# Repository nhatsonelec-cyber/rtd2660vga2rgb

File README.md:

# RTD2660 VGA (header 12P) → LVDS 20P cho màn 7" 1024x600

Mạch điều khiển màn hình dùng chip Realtek **RTD2660**, thiết kế theo datasheet trong repo (`RTD2660.jsp.pdf`).

- **Đầu vào:** VGA trên **header 12 chân 2.54 mm**, cắm thẳng vào header VGA trên mainboard.
- **Đầu ra:** LVDS 1 kênh, 24 bit trên **đầu 20 chân 2.0 mm (J5)**, cùng **đầu đèn nền 4 chân 2.0 mm (J6)**.
  Hai đầu này khớp với cáp của màn 7" IPS 1024x600 LVDS 20 chân (Huadi).
- **Bản RGB 40P/50P tạm bỏ.** Mạch của chúng vẫn còn trong `tools/circuit.py` để làm sau.

| File | Nội dung |
|---|---|
| `eagle/RTD2660_VGA12P_LVDS.sch` | Sơ đồ nguyên lý, 4 trang |
| `eagle/RTD2660_VGA12P_LVDS.brd` | Board 120 x 80 mm, linh kiện đã đặt ở mặt trên, chưa đi dây |
| `eagle/rtd2660_board.lbr` | Thư viện linh kiện |
| `eagle/RTD2660_VGA12P_LVDS_BOM.csv` | Danh sách linh kiện |
| `preview/RTD2660_VGA12P_LVDS_preview.pdf` | Bản xem trước sơ đồ và board |
| `firmware/` | Script cấu hình firmware cho SDK RTD2660 |

## Trạng thái

- **Sơ đồ nguyên lý: xong.** Các net nối bằng nhãn tên.
- **Board: toàn bộ 114 linh kiện đặt ở mặt trên, chưa đi dây.** Có sẵn polygon GND ở mặt dưới.
- Mở bằng Eagle 7.x, 8.x hoặc 9.x. File `.brd` mở kèm và nhất quán với sơ đồ.
- **Đã kiểm tra:** KiCad đọc được file `.brd`, netlist khớp 100% từng pad với sơ đồ. DRC không có linh kiện chồng nhau.
  `tools/check_eagle.py` xác nhận mọi chân nằm trên lưới 0.1 inch.
- Khi đi dây, đi các cặp LVDS thành cặp vi sai 100 Ω, ngắn và bằng chiều dài. Thêm via tản nhiệt dưới pad GND của RTD2660.

## Sơ đồ chân các đầu nối

**J2 - VGA 1x12, 2.54 mm (đầu vào)**

| Chân | Tín hiệu |
|---|---|
| 1 | VGA_R |
| 2 | GND |
| 3 | VGA_G |
| 4 | GND |
| 5 | VGA_B |
| 6 | GND |
| 7 | VGA_HS |
| 8 | VGA_VS |
| 9 | GND |
| 10 | VGA_SDA |
| 11 | VGA_SCL |
| 12 | VGA_5V |

Chân 12 (+5V từ mainboard) không dùng. Nếu header VGA trên mainboard có thứ tự khác, sửa `VGA12_PINOUT` trong `tools/circuit.py`.

**J5 - LVDS 1x20, 2.0 mm (đầu đen của cáp màn)**

| Chân | Tín hiệu |
|---|---|
| 1 | VLCD |
| 2 | VLCD |
| 3 | PNL_LED_EN |
| 4 | GND |
| 5 | LVDS_E0- |
| 6 | LVDS_E0+ |
| 7 | GND |
| 8 | LVDS_E1- |
| 9 | LVDS_E1+ |
| 10 | GND |
| 11 | LVDS_E2- |
| 12 | LVDS_E2+ |
| 13 | GND |
| 14 | LVDS_EC- |
| 15 | LVDS_EC+ |
| 16 | GND |
| 17 | LVDS_E3- |
| 18 | LVDS_E3+ |
| 19 | không dùng |
| 20 | không dùng |

Chân 1-18 giống hệt sơ đồ chân của màn. Ở chế độ 1 kênh, RTD2660 xuất trên các cặp E (chân 86-95 của chip).

**J6 - đèn nền 1x4, 2.0 mm (đầu trắng của cáp màn)**

| Chân | Tín hiệu |
|---|---|
| 1 | +12V |
| 2 | PNL_LED_EN |
| 3 | PNL_BL_ADJ |
| 4 | GND |

**Thứ tự chân J6 là giả định.** Hãy đo cáp bằng đồng hồ: VLED nối chân 20 của màn, PWM nối chân 19, LED_EN nối chân 3.
Nếu khác, sửa `BL4_PINOUT` trong `tools/circuit.py` rồi chạy lại script.

- Chân độ sáng ra điện áp DC từ 0 đến 1.41 V, lấy từ PWM4 qua bộ lọc 10k / 7.5k / 1 µF. Màn nhận 0.7 đến 1.4 V.
- LED_EN lấy từ BL_ON qua 1k, có 10k kéo xuống.
- VLED lấy thẳng từ +12 V. Màn nhận 5 đến 12 V.

Các đầu nối khác:

- **J1, nguồn vào 12 V:** 1 = +12V, 2 = GND. Có cầu chì PTC 2 A và diode chống ngược.
- **J3, nạp firmware qua DDC:** GND, SDA, SCL.
- **J4, phím và IR (1x8):** 1 +3V3, 2 GND, 3 KEY_AD0, 4 KEY_AD1, 5 IR, 6 LED_G, 7 LED_R, 8 +5V.

## Nguồn

12 V → LM2596S-5.0 → 5 V. Từ 5 V có hai AMS1117-3.3: một cho phần số (PVCC, flash) và một cho phần analog (VDD, VADC).
Từ đó hai AMS1117-1.8 tạo VCCK (lõi) và ADC_VDD.
VDD 3.3 V của màn lấy từ một AMS1117-3.3 riêng, được bật bằng MOSFET AO3401A theo chân PANEL_ON.

## Bàn phím (J4)

SDK đọc phím bằng một kênh ADC 6 bit (KEY_AD0, chân 50). Trên board đã có điện trở kéo lên 10k.
Trên bo phím, mỗi nút nối KEY_AD0 xuống GND qua một điện trở:

| Nút | Điện trở xuống GND | Mã ADC |
|---|---|---|
| POWER | 0 Ω | 0 |
| MENU | 1.8k | 10 |
| RIGHT | 3.9k | 18 |
| LEFT | 8.2k | 28 |
| SOURCE | 22k | 43 |

## Gán chân GPIO

| Chân | Chức năng chip | Net | Dùng cho |
|---|---|---|---|
| 50 | P6.0 / A-ADC0 | KEY_AD0 | Keypad resistor ladder 1 (ADC) |
| 51 | P6.1 / A-ADC1 | KEY_AD1 | Keypad resistor ladder 2 (ADC) |
| 52 | P6.2 | LED_R_DRV | Red / standby LED, active high |
| 53 | P6.3 | LED_G_DRV | Green / power LED, active high |
| 58 | DDCSCL1 (P3.0) | DDC_SCL | VGA DDC clock, ISP programming |
| 59 | DDCSDA1 (P3.1) | DDC_SDA | VGA DDC data, ISP programming |
| 98 | P5.4 | PANEL_ON | Panel power enable, active high |
| 99 | P5.5 | BL_ON | Backlight enable, active high |
| 100 | P5.6 / PWM4 | BL_PWM | Backlight brightness PWM, high = bright |
| 113 | P3.6 / IrDA | IR_IN | IR receiver input |

## Firmware

RTD2660 cần firmware trong flash W25Q40. Xem `firmware/README.md`.
Script áp cấu hình board và màn 1024x600 lên SDK RTD2660, sau đó biên dịch bằng Keil C51.

## Những điểm cần kiểm tra

1. **Thạch anh 27 MHz**, giống board tham chiếu PCB800099 của SDK.
2. **Chân SPI flash.** Tên chân (115 SCLK, 116 SI, 117 SO) và phần mô tả trong datasheet lệch nhau ở chân 115/116.
   Mạch theo tên chân. Có sẵn cặp điện trở 33R (không hàn) để đảo CLK/DI nếu flash không chạy.
3. **Thứ tự chân header VGA 12P và đầu đèn nền 4 chân.** Phải khớp với mainboard và cáp màn.
4. **Timing màn** (tổng 1344 x 635, 51.2 MHz) là giá trị phổ biến của màn 7" 1024x600. Nếu có datasheet màn, đối chiếu lại.

## Sửa thiết kế

```bash
pip install lxml matplotlib
python3 tools/gen_eagle.py      # sinh file Eagle và BOM
python3 tools/check_eagle.py    # kiểm tra
python3 tools/preview.py        # sinh bản xem trước PDF
```

- `tools/circuit.py`: mạch điện, sơ đồ chân các đầu nối, bảng GPIO
- `tools/parts.py`: ký hiệu, footprint, sơ đồ chân RTD2660
- `tools/gen_eagle.py`: ghi file Eagle và đặt linh kiện trên board
- `firmware/apply_board.py`: áp cấu hình board và màn lên SDK firmware RTD2660

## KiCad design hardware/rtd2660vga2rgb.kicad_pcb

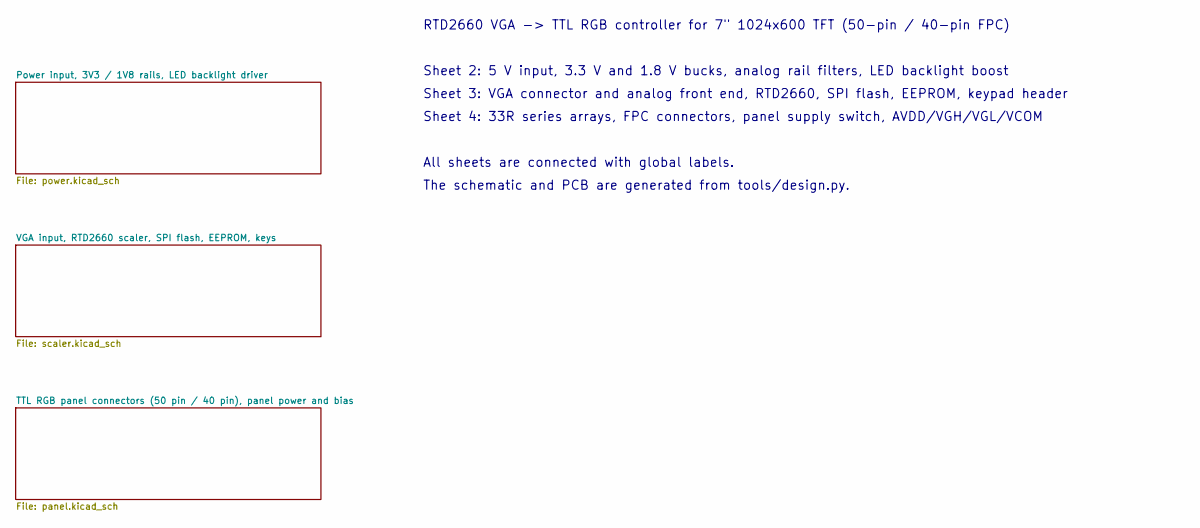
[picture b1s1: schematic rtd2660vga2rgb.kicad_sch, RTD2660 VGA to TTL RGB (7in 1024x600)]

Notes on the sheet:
RTD2660 VGA -> TTL RGB controller for 7" 1024x600 TFT (50-pin / 40-pin FPC)
Sheet 2: 5 V input, 3.3 V and 1.8 V bucks, analog rail filters, LED backlight boost
Sheet 3: VGA connector and analog front end, RTD2660, SPI flash, EEPROM, keypad header
Sheet 4: 33R series arrays, FPC connectors, panel supply switch, AVDD/VGH/VGL/VCOM
All sheets are connected with global labels.
The schematic and PCB are generated from tools/design.py.

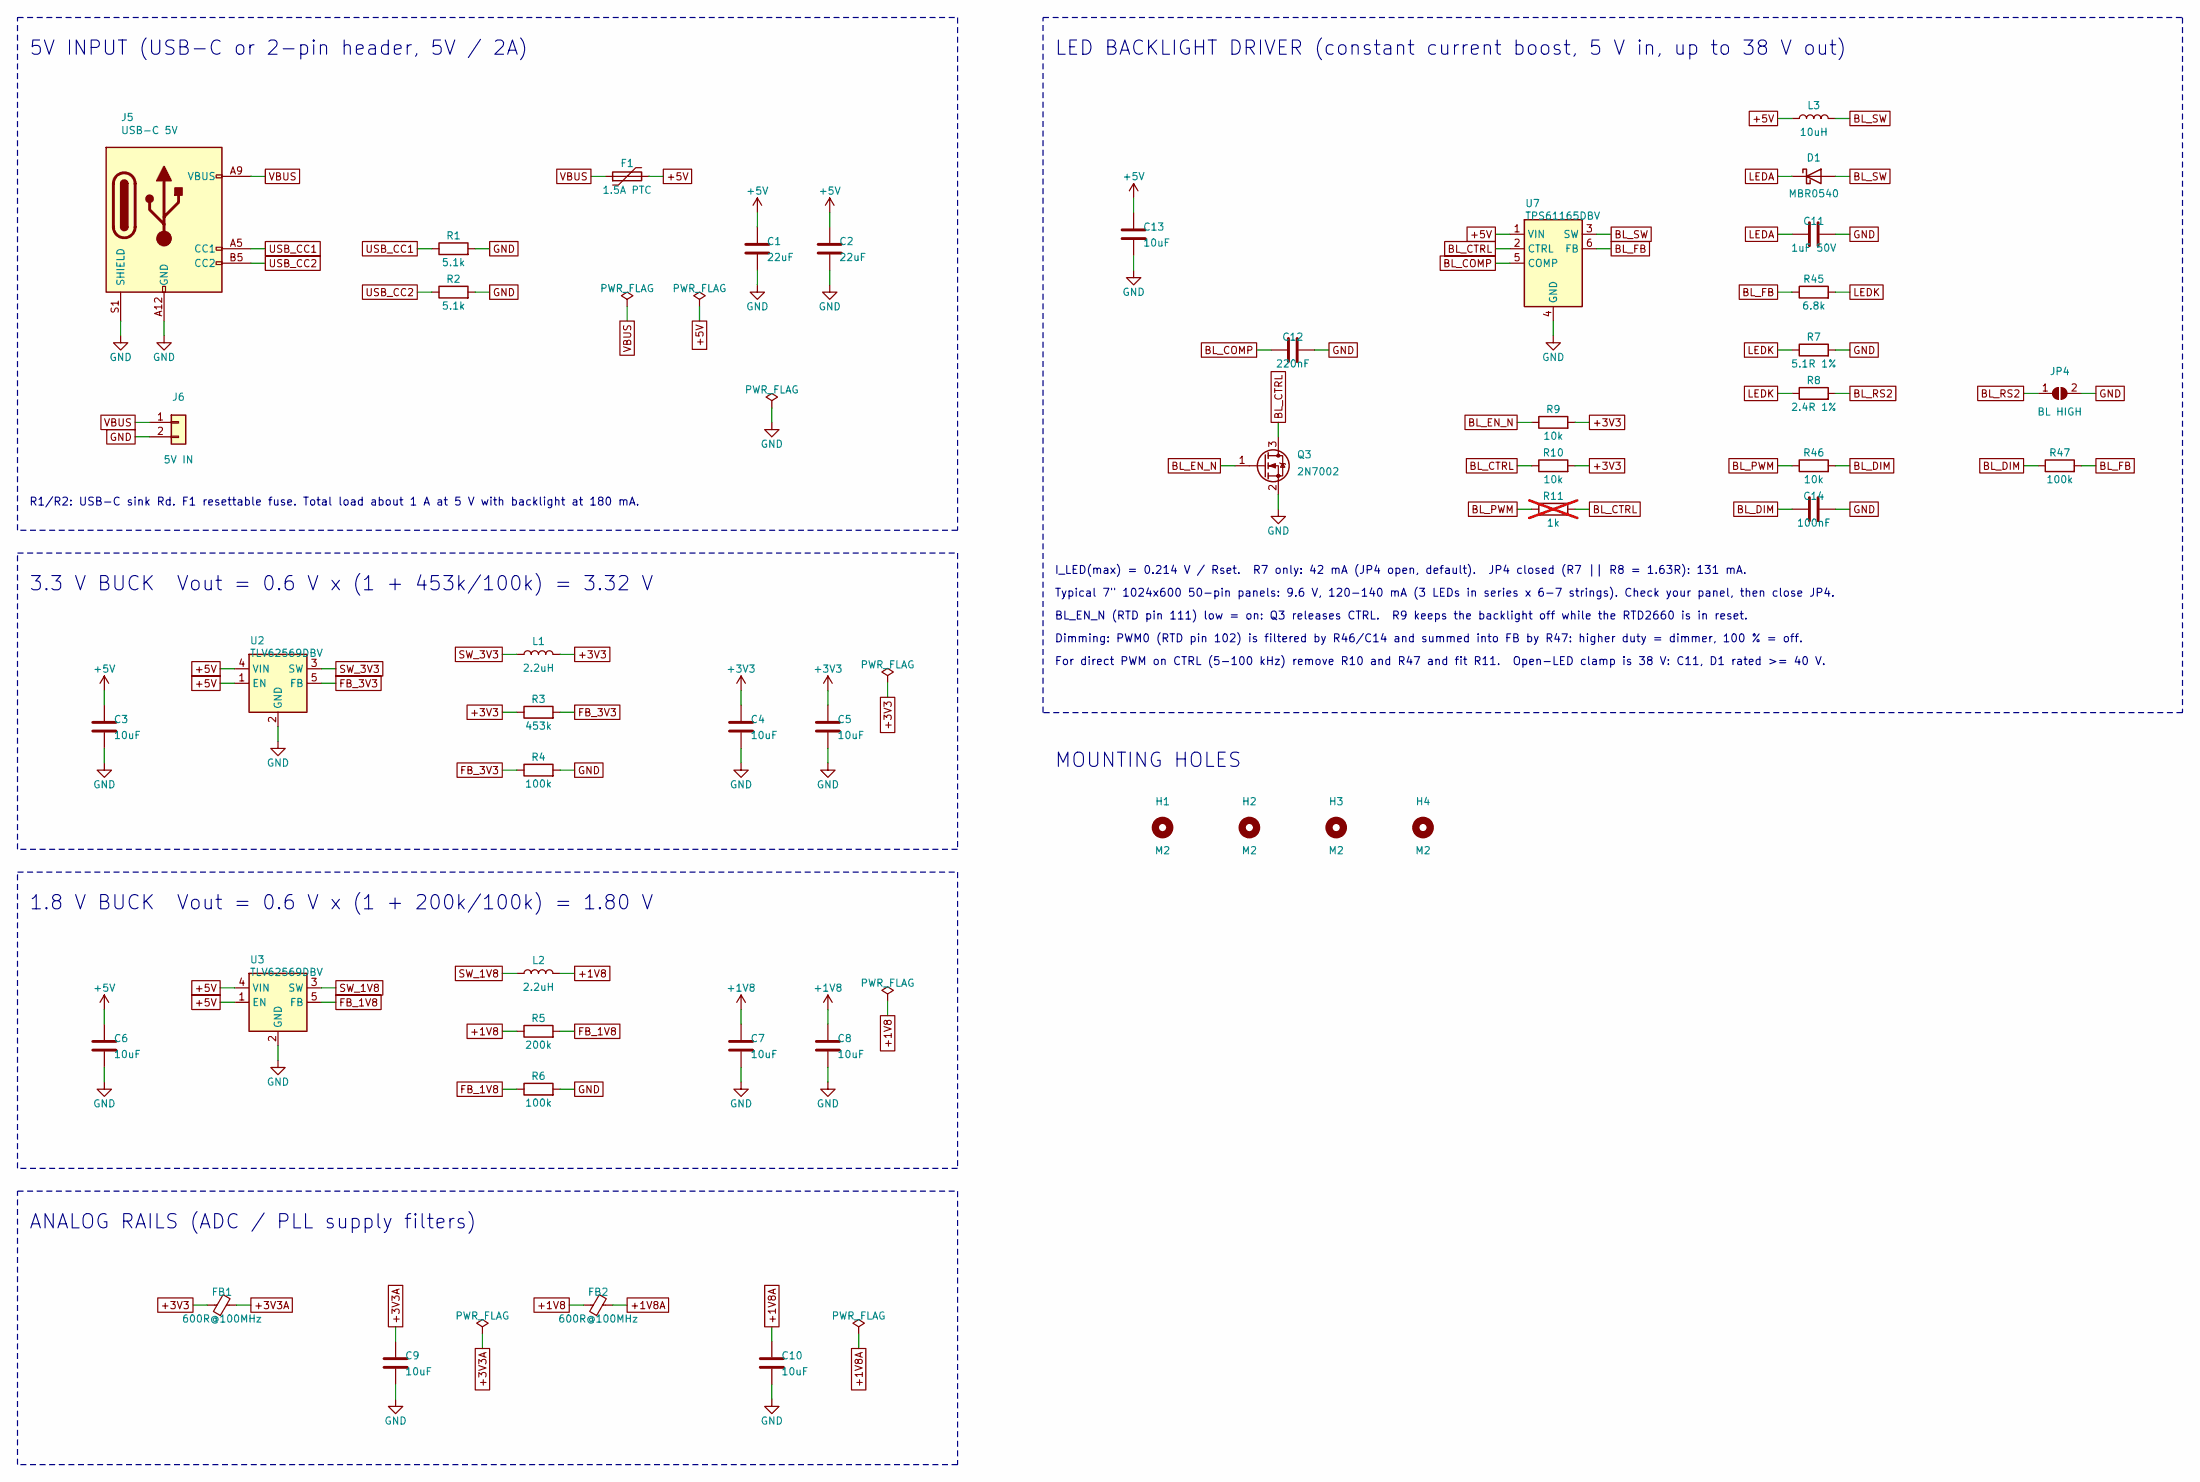
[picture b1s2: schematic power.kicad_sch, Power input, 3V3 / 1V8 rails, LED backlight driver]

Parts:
C1, C2: 22uF; C_0805_2012Metric
C3, C4, C5, C6, C7, C8, C9, C10, C13: 10uF; C_0805_2012Metric
C11: 1uF 50V; C_0805_2012Metric
C12: 220nF; C_0603_1608Metric
C14: 100nF; C_0603_1608Metric
D1: MBR0540; D_SOD-123
F1: 1.5A PTC; Fuse_1206_3216Metric
FB1, FB2: 600R@100MHz; L_0603_1608Metric
H1, H2, H3, H4: M2; MountingHole_2.2mm_M2
J5: USB-C 5V; USB_C_Receptacle_GCT_USB4125-xx-x_6P_TopMnt_Horizontal
J6: 5V IN; PinHeader_1x02_P2.54mm_Vertical
JP4: BL HIGH; SolderJumper-2_P1.3mm_Open_RoundedPad1.0x1.5mm
L1, L2: 2.2uH; L_Taiyo-Yuden_NR-30xx
L3: 10uH; L_Taiyo-Yuden_NR-40xx
Q3: 2N7002; SOT-23
R1, R2: 5.1k; R_0603_1608Metric
R3: 453k; R_0603_1608Metric
R4, R6, R47: 100k; R_0603_1608Metric
R5: 200k; R_0603_1608Metric
R7: 5.1R 1%; R_0603_1608Metric
R8: 2.4R 1%; R_0603_1608Metric
R9, R10, R46: 10k; R_0603_1608Metric
R11: 1k; R_0603_1608Metric; not fitted
R45: 6.8k; R_0603_1608Metric
U2, U3: TLV62569DBV; SOT-23-5
U7: TPS61165DBV; SOT-23-6

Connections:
+1V8: C7.1, C8.1, FB2.1, L2.2, R5.1; also elsewhere on the board
+1V8A: C10.1, FB2.2; also elsewhere on the board
+3V3: C4.1, C5.1, FB1.1, L1.2, R3.1, R9.2, R10.2; also elsewhere on the board
+3V3A: C9.1, FB1.2; also elsewhere on the board
+5V: C1.1, C2.1, C3.1, C6.1, C13.1, F1.2, L3.1, U2.1 (EN), U2.4 (VIN), U3.1 (EN), U3.4 (VIN), U7.1 (VIN); also elsewhere on the board
BL_COMP: C12.1, U7.5 (COMP)
BL_CTRL: Q3.3 (D), R10.1, R11.2, U7.2 (CTRL)
BL_DIM: C14.1, R46.2, R47.1
BL_EN_N: Q3.1 (G), R9.1; also elsewhere on the board
BL_FB: R45.1, R47.2, U7.6 (FB)
BL_PWM: R11.1, R46.1; also elsewhere on the board
BL_RS2: JP4.1 (A), R8.2
BL_SW: D1.2 (A), L3.2, U7.3 (SW)
FB_1V8: R5.2, R6.1, U3.5 (FB)
FB_3V3: R3.2, R4.1, U2.5 (FB)
GND: C1.2, C2.2, C3.2, C4.2, C5.2, C6.2, C7.2, C8.2, C9.2, C10.2, C11.2, C12.2, C13.2, C14.2, J5.A12 (GND), J5.B12 (GND), J5.S1 (SHIELD), J6.2, JP4.2 (B), Q3.2 (S), R1.2, R2.2, R4.2, R6.2, R7.2, U2.2 (GND), U3.2 (GND), U7.4 (GND); also elsewhere on the board
LEDA: C11.1, D1.1 (K); also elsewhere on the board
LEDK: R7.1, R8.1, R45.2; also elsewhere on the board
SW_1V8: L2.1, U3.3 (SW)
SW_3V3: L1.1, U2.3 (SW)
USB_CC1: J5.A5 (CC1), R1.1
USB_CC2: J5.B5 (CC2), R2.1
VBUS: F1.1, J5.A9 (VBUS), J5.B9 (VBUS), J6.1

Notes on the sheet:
5V INPUT (USB-C or 2-pin header, 5V / 2A)
R1/R2: USB-C sink Rd. F1 resettable fuse. Total load about 1 A at 5 V with backlight at 180 mA.
3.3 V BUCK Vout = 0.6 V x (1 + 453k/100k) = 3.32 V
1.8 V BUCK Vout = 0.6 V x (1 + 200k/100k) = 1.80 V
ANALOG RAILS (ADC / PLL supply filters)
LED BACKLIGHT DRIVER (constant current boost, 5 V in, up to 38 V out)
I_LED(max) = 0.214 V / Rset. R7 only: 42 mA (JP4 open, default). JP4 closed (R7 || R8 = 1.63R): 131 mA.
Typical 7" 1024x600 50-pin panels: 9.6 V, 120-140 mA (3 LEDs in series x 6-7 strings). Check your panel, then close JP4.
BL_EN_N (RTD pin 111) low = on: Q3 releases CTRL. R9 keeps the backlight off while the RTD2660 is in reset.
Dimming: PWM0 (RTD pin 102) is filtered by R46/C14 and summed into FB by R47: higher duty = dimmer, 100 % = off.
For direct PWM on CTRL (5-100 kHz) remove R10 and R47 and fit R11. Open-LED clamp is 38 V: C11, D1 rated >= 40 V.
MOUNTING HOLES

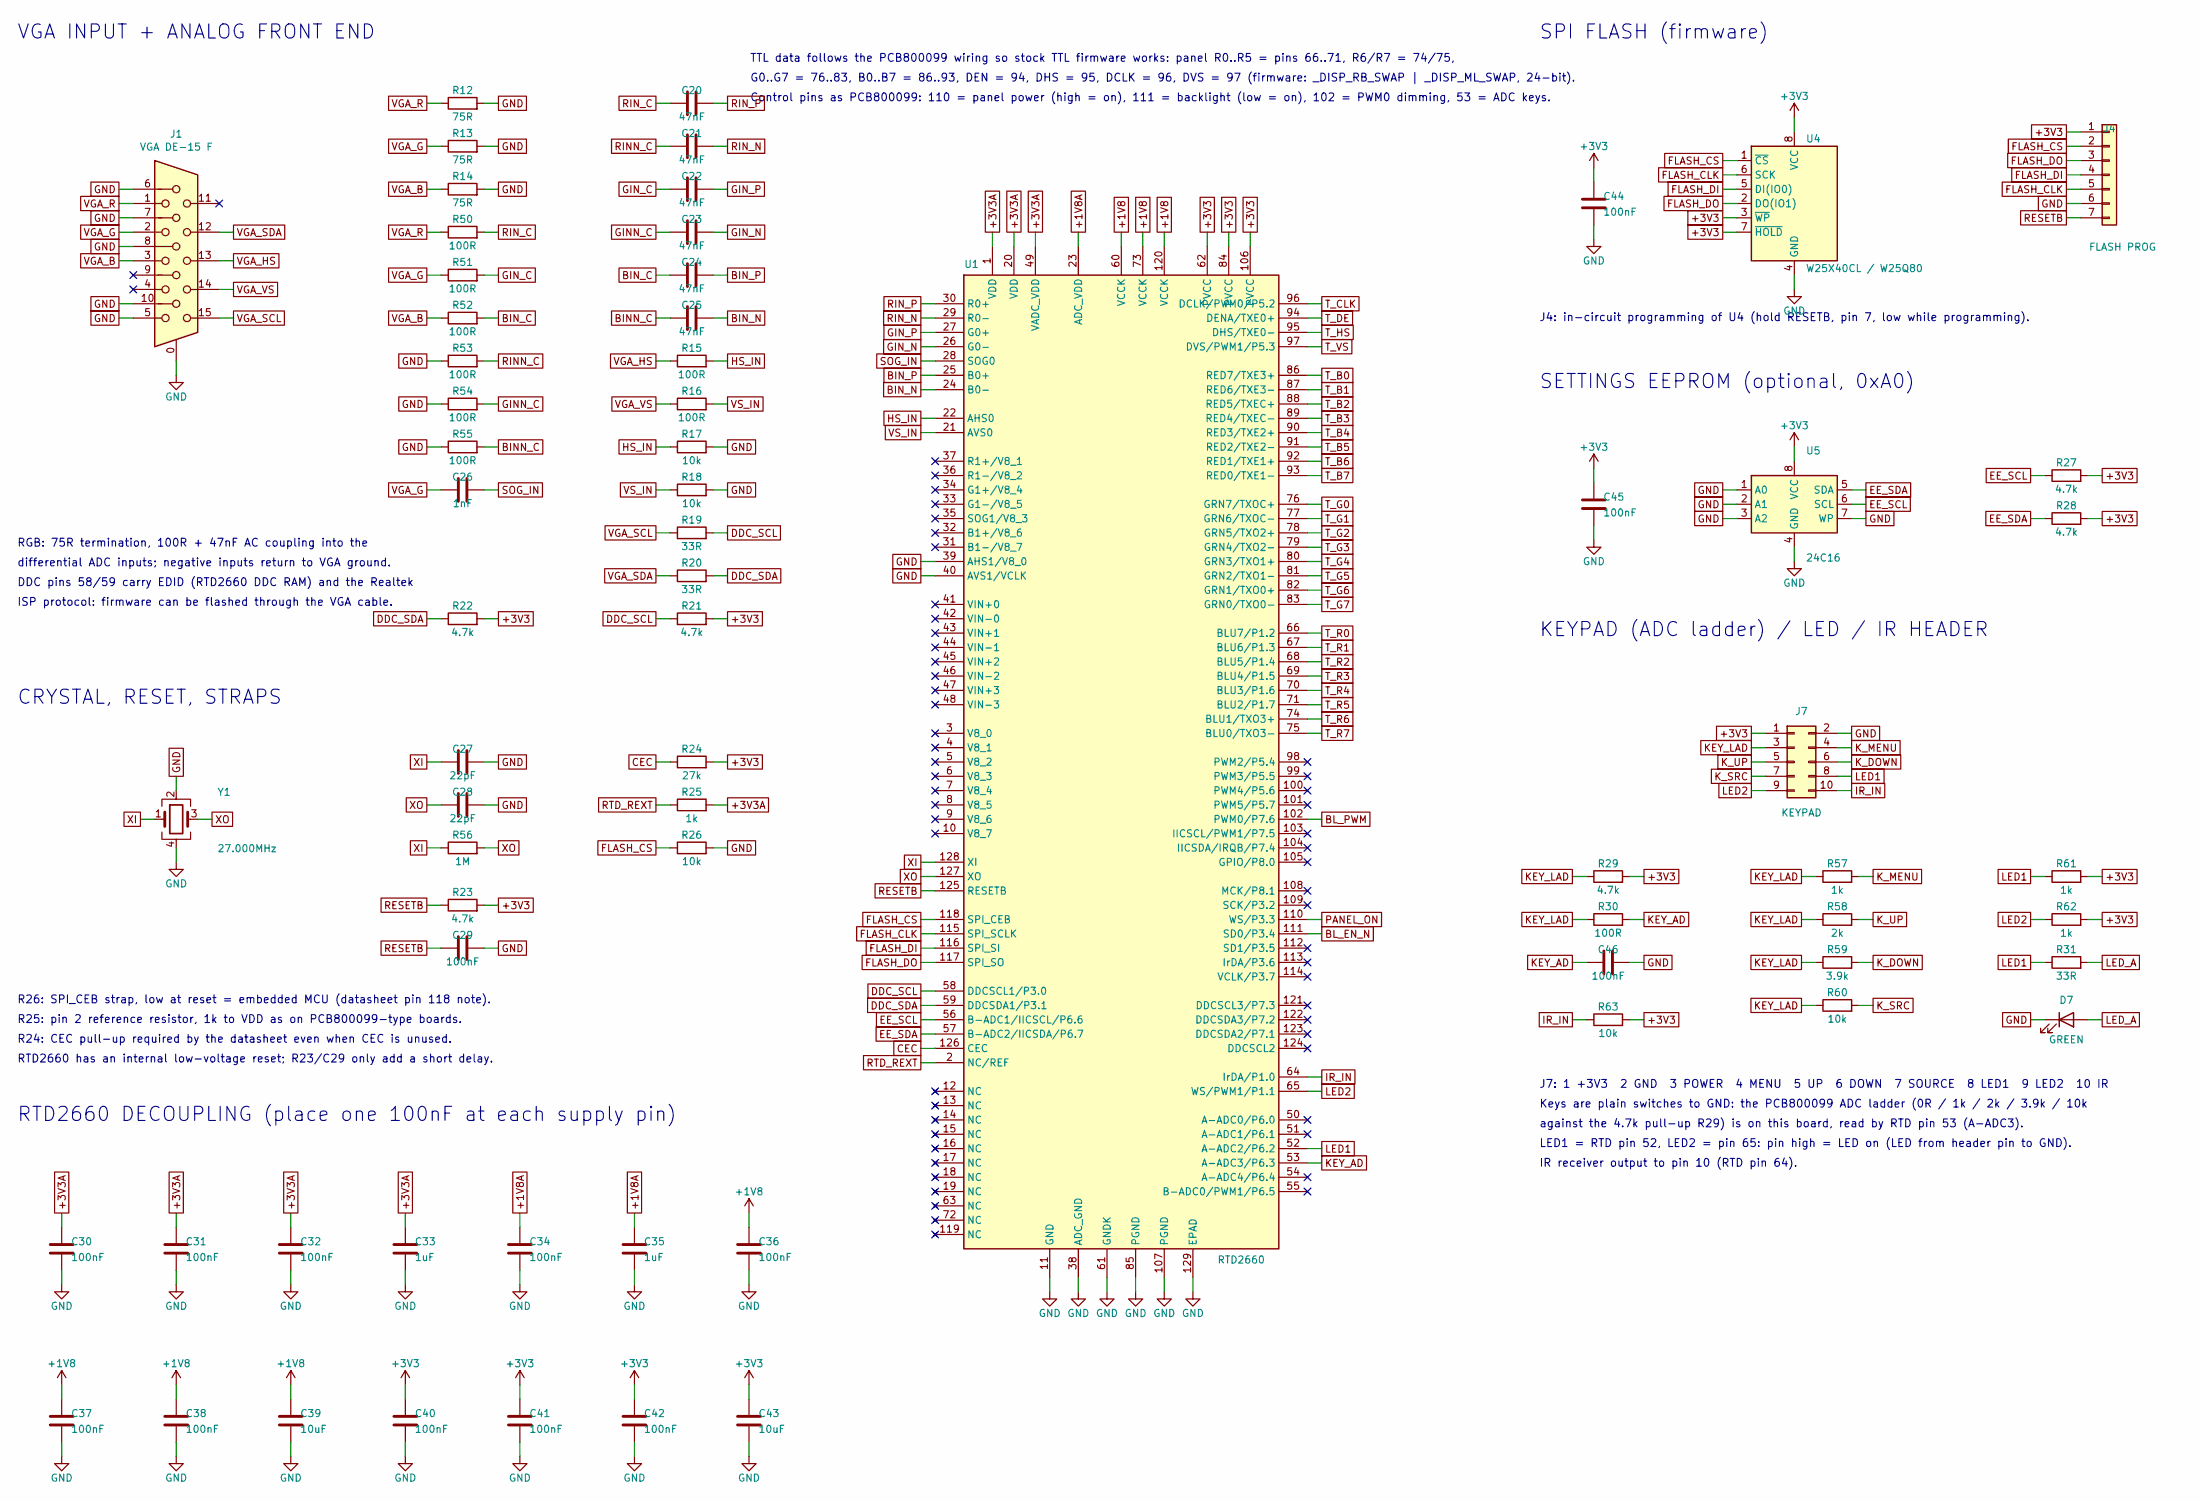
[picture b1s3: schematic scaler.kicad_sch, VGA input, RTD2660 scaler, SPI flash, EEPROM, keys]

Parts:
C20, C21, C22, C23, C24, C25: 47nF; C_0603_1608Metric
C26: 1nF; C_0603_1608Metric
C27, C28: 22pF; C_0603_1608Metric
C29, C30, C31, C32, C34, C36, C37, C38, C40, C41, C42, C44, C45, C46: 100nF; C_0603_1608Metric
C33, C35: 1uF; C_0603_1608Metric
C39, C43: 10uF; C_0805_2012Metric
D7: GREEN; LED_0603_1608Metric
J1: VGA DE-15 F; DSUB-15-HD_Female_Horizontal_P2.29x1.98mm_EdgePinOffset3.03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
J4: FLASH PROG; PinHeader_1x07_P1.27mm_Vertical
J7: KEYPAD; PinHeader_2x05_P1.27mm_Vertical_SMD
R12, R13, R14: 75R; R_0603_1608Metric
R15, R16, R30, R50, R51, R52, R53, R54, R55: 100R; R_0603_1608Metric
R17, R18, R26, R60, R63: 10k; R_0603_1608Metric
R19, R20, R31: 33R; R_0603_1608Metric
R21, R22, R23, R27, R28, R29: 4.7k; R_0603_1608Metric
R24: 27k; R_0603_1608Metric
R25, R57, R61, R62: 1k; R_0603_1608Metric
R56: 1M; R_0603_1608Metric
R58: 2k; R_0603_1608Metric
R59: 3.9k; R_0603_1608Metric
U1: RTD2660; LQFP-128-1EP_14x20mm_P0.5mm_EP7.1x7.1mm
U4: W25X40CL / W25Q80; SOIC-8_3.9x4.9mm_P1.27mm
U5: 24C16; SOIC-8_3.9x4.9mm_P1.27mm
Y1: 27.000MHz; Crystal_SMD_3225-4Pin_3.2x2.5mm

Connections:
+1V8: C36.1, C37.1, C38.1, C39.1, U1.60 (VCCK), U1.73 (VCCK), U1.120 (VCCK); also elsewhere on the board
+1V8A: C34.1, C35.1, U1.23 (ADC_VDD); also elsewhere on the board
+3V3: C40.1, C41.1, C42.1, C43.1, C44.1, C45.1, J4.1, J7.1, R21.2, R22.2, R23.2, R24.2, R27.2, R28.2, R29.2, R61.2, R62.2, R63.2, U1.62 (PVCC), U1.84 (PVCC), U1.106 (PVCC), U4.3 (~WP), U4.7 (~HOLD), U4.8 (VCC), U5.8 (VCC); also elsewhere on the board
+3V3A: C30.1, C31.1, C32.1, C33.1, R25.2, U1.1 (VDD), U1.20 (VDD), U1.49 (VADC_VDD); also elsewhere on the board
BINN_C: C25.1, R55.2
BIN_C: C24.1, R52.2
BIN_N: C25.2, U1.24 (B0-)
BIN_P: C24.2, U1.25 (B0+)
BL_EN_N: U1.111 (SD0/P3.4); also elsewhere on the board
BL_PWM: U1.102 (PWM0/P7.6); also elsewhere on the board
CEC: R24.1, U1.126 (CEC)
DDC_SCL: R19.2, R21.1, U1.58 (DDCSCL1/P3.0)
DDC_SDA: R20.2, R22.1, U1.59 (DDCSDA1/P3.1)
EE_SCL: R27.1, U1.56 (B-ADC1/IICSCL/P6.6), U5.6 (SCL)
EE_SDA: R28.1, U1.57 (B-ADC2/IICSDA/P6.7), U5.5 (SDA)
FLASH_CLK: J4.5, U1.115 (SPI_SCLK), U4.6 (SCK)
FLASH_CS: J4.2, R26.1, U1.118 (SPI_CEB), U4.1 (~CS)
FLASH_DI: J4.4, U1.116 (SPI_SI), U4.5 (DI(IO0))
FLASH_DO: J4.3, U1.117 (SPI_SO), U4.2 (DO(IO1))
GINN_C: C23.1, R54.2
GIN_C: C22.1, R51.2
GIN_N: C23.2, U1.26 (G0-)
GIN_P: C22.2, U1.27 (G0+)
GND: C27.2, C28.2, C29.2, C30.2, C31.2, C32.2, C33.2, C34.2, C35.2, C36.2, C37.2, C38.2, C39.2, C40.2, C41.2, C42.2, C43.2, C44.2, C45.2, C46.2, D7.1 (K), J1.0, J1.5, J1.6, J1.7, J1.8, J1.10, J4.6, J7.2, R12.2, R13.2, R14.2, R17.2, R18.2, R26.2, R53.1, R54.1, R55.1, U1.11 (GND), U1.38 (ADC_GND), U1.39 (AHS1/V8_0), U1.40 (AVS1/VCLK), U1.61 (GNDK), U1.85 (PGND), U1.107 (PGND), U1.129 (EPAD), U4.4 (GND), U5.1 (A0), U5.2 (A1), U5.3 (A2), U5.4 (GND), U5.7 (WP), Y1.2, Y1.4; also elsewhere on the board
HS_IN: R15.2, R17.1, U1.22 (AHS0)
IR_IN: J7.10, R63.1, U1.64 (IrDA/P1.0)
KEY_AD: C46.1, R30.2, U1.53 (A-ADC3/P6.3)
KEY_LAD: J7.3, R29.1, R30.1, R57.1, R58.1, R59.1, R60.1
K_DOWN: J7.6, R59.2
K_MENU: J7.4, R57.2
K_SRC: J7.7, R60.2
K_UP: J7.5, R58.2
LED1: J7.8, R31.1, R61.1, U1.52 (A-ADC2/P6.2)
LED2: J7.9, R62.1, U1.65 (WS/PWM1/P1.1)
LED_A: D7.2 (A), R31.2
PANEL_ON: U1.110 (WS/P3.3); also elsewhere on the board
RESETB: C29.1, J4.7, R23.1, U1.125 (RESETB)
RINN_C: C21.1, R53.2
RIN_C: C20.1, R50.2
RIN_N: C21.2, U1.29 (R0-)
RIN_P: C20.2, U1.30 (R0+)
RTD_REXT: R25.1, U1.2 (NC/REF)
SOG_IN: C26.2, U1.28 (SOG0)
T_B0: U1.86 (RED7/TXE3+); also elsewhere on the board
T_B1: U1.87 (RED6/TXE3-); also elsewhere on the board
T_B2: U1.88 (RED5/TXEC+); also elsewhere on the board
T_B3: U1.89 (RED4/TXEC-); also elsewhere on the board
T_B4: U1.90 (RED3/TXE2+); also elsewhere on the board
T_B5: U1.91 (RED2/TXE2-); also elsewhere on the board
T_B6: U1.92 (RED1/TXE1+); also elsewhere on the board
T_B7: U1.93 (RED0/TXE1-); also elsewhere on the board
T_CLK: U1.96 (DCLK/PWM0/P5.2); also elsewhere on the board
T_DE: U1.94 (DENA/TXE0+); also elsewhere on the board
T_G0: U1.76 (GRN7/TXOC+); also elsewhere on the board
T_G1: U1.77 (GRN6/TXOC-); also elsewhere on the board
T_G2: U1.78 (GRN5/TXO2+); also elsewhere on the board
T_G3: U1.79 (GRN4/TXO2-); also elsewhere on the board
T_G4: U1.80 (GRN3/TXO1+); also elsewhere on the board
T_G5: U1.81 (GRN2/TXO1-); also elsewhere on the board
T_G6: U1.82 (GRN1/TXO0+); also elsewhere on the board
T_G7: U1.83 (GRN0/TXO0-); also elsewhere on the board
T_HS: U1.95 (DHS/TXE0-); also elsewhere on the board
T_R0: U1.66 (BLU7/P1.2); also elsewhere on the board
T_R1: U1.67 (BLU6/P1.3); also elsewhere on the board
T_R2: U1.68 (BLU5/P1.4); also elsewhere on the board
T_R3: U1.69 (BLU4/P1.5); also elsewhere on the board
T_R4: U1.70 (BLU3/P1.6); also elsewhere on the board
T_R5: U1.71 (BLU2/P1.7); also elsewhere on the board
T_R6: U1.74 (BLU1/TXO3+); also elsewhere on the board
T_R7: U1.75 (BLU0/TXO3-); also elsewhere on the board
T_VS: U1.97 (DVS/PWM1/P5.3); also elsewhere on the board
VGA_B: J1.3, R14.1, R52.1
VGA_G: C26.1, J1.2, R13.1, R51.1
VGA_HS: J1.13, R15.1
VGA_R: J1.1, R12.1, R50.1
VGA_SCL: J1.15, R19.1
VGA_SDA: J1.12, R20.1
VGA_VS: J1.14, R16.1
VS_IN: R16.2, R18.1, U1.21 (AVS0)
XI: C27.1, R56.1, U1.128 (XI), Y1.1
XO: C28.1, R56.2, U1.127 (XO), Y1.3

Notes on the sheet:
VGA INPUT + ANALOG FRONT END
RGB: 75R termination, 100R + 47nF AC coupling into the
differential ADC inputs; negative inputs return to VGA ground.
DDC pins 58/59 carry EDID (RTD2660 DDC RAM) and the Realtek
ISP protocol: firmware can be flashed through the VGA cable.
CRYSTAL, RESET, STRAPS
R26: SPI_CEB strap, low at reset = embedded MCU (datasheet pin 118 note).
R25: pin 2 reference resistor, 1k to VDD as on PCB800099-type boards.
R24: CEC pull-up required by the datasheet even when CEC is unused.
RTD2660 has an internal low-voltage reset; R23/C29 only add a short delay.
RTD2660 DECOUPLING (place one 100nF at each supply pin)
TTL data follows the PCB800099 wiring so stock TTL firmware works: panel R0..R5 = pins 66..71, R6/R7 = 74/75,
G0..G7 = 76..83, B0..B7 = 86..93, DEN = 94, DHS = 95, DCLK = 96, DVS = 97 (firmware: _DISP_RB_SWAP | _DISP_ML_SWAP, 24-bit).
Control pins as PCB800099: 110 = panel power (high = on), 111 = backlight (low = on), 102 = PWM0 dimming, 53 = ADC keys.
SPI FLASH (firmware)
J4: in-circuit programming of U4 (hold RESETB, pin 7, low while programming).
SETTINGS EEPROM (optional, 0xA0)
KEYPAD (ADC ladder) / LED / IR HEADER
J7: 1 +3V3 2 GND 3 POWER 4 MENU 5 UP 6 DOWN 7 SOURCE 8 LED1 9 LED2 10 IR
Keys are plain switches to GND: the PCB800099 ADC ladder (0R / 1k / 2k / 3.9k / 10k
against the 4.7k pull-up R29) is on this board, read by RTD pin 53 (A-ADC3).
LED1 = RTD pin 52, LED2 = pin 65: pin high = LED on (LED from header pin to GND).
IR receiver output to pin 10 (RTD pin 64).

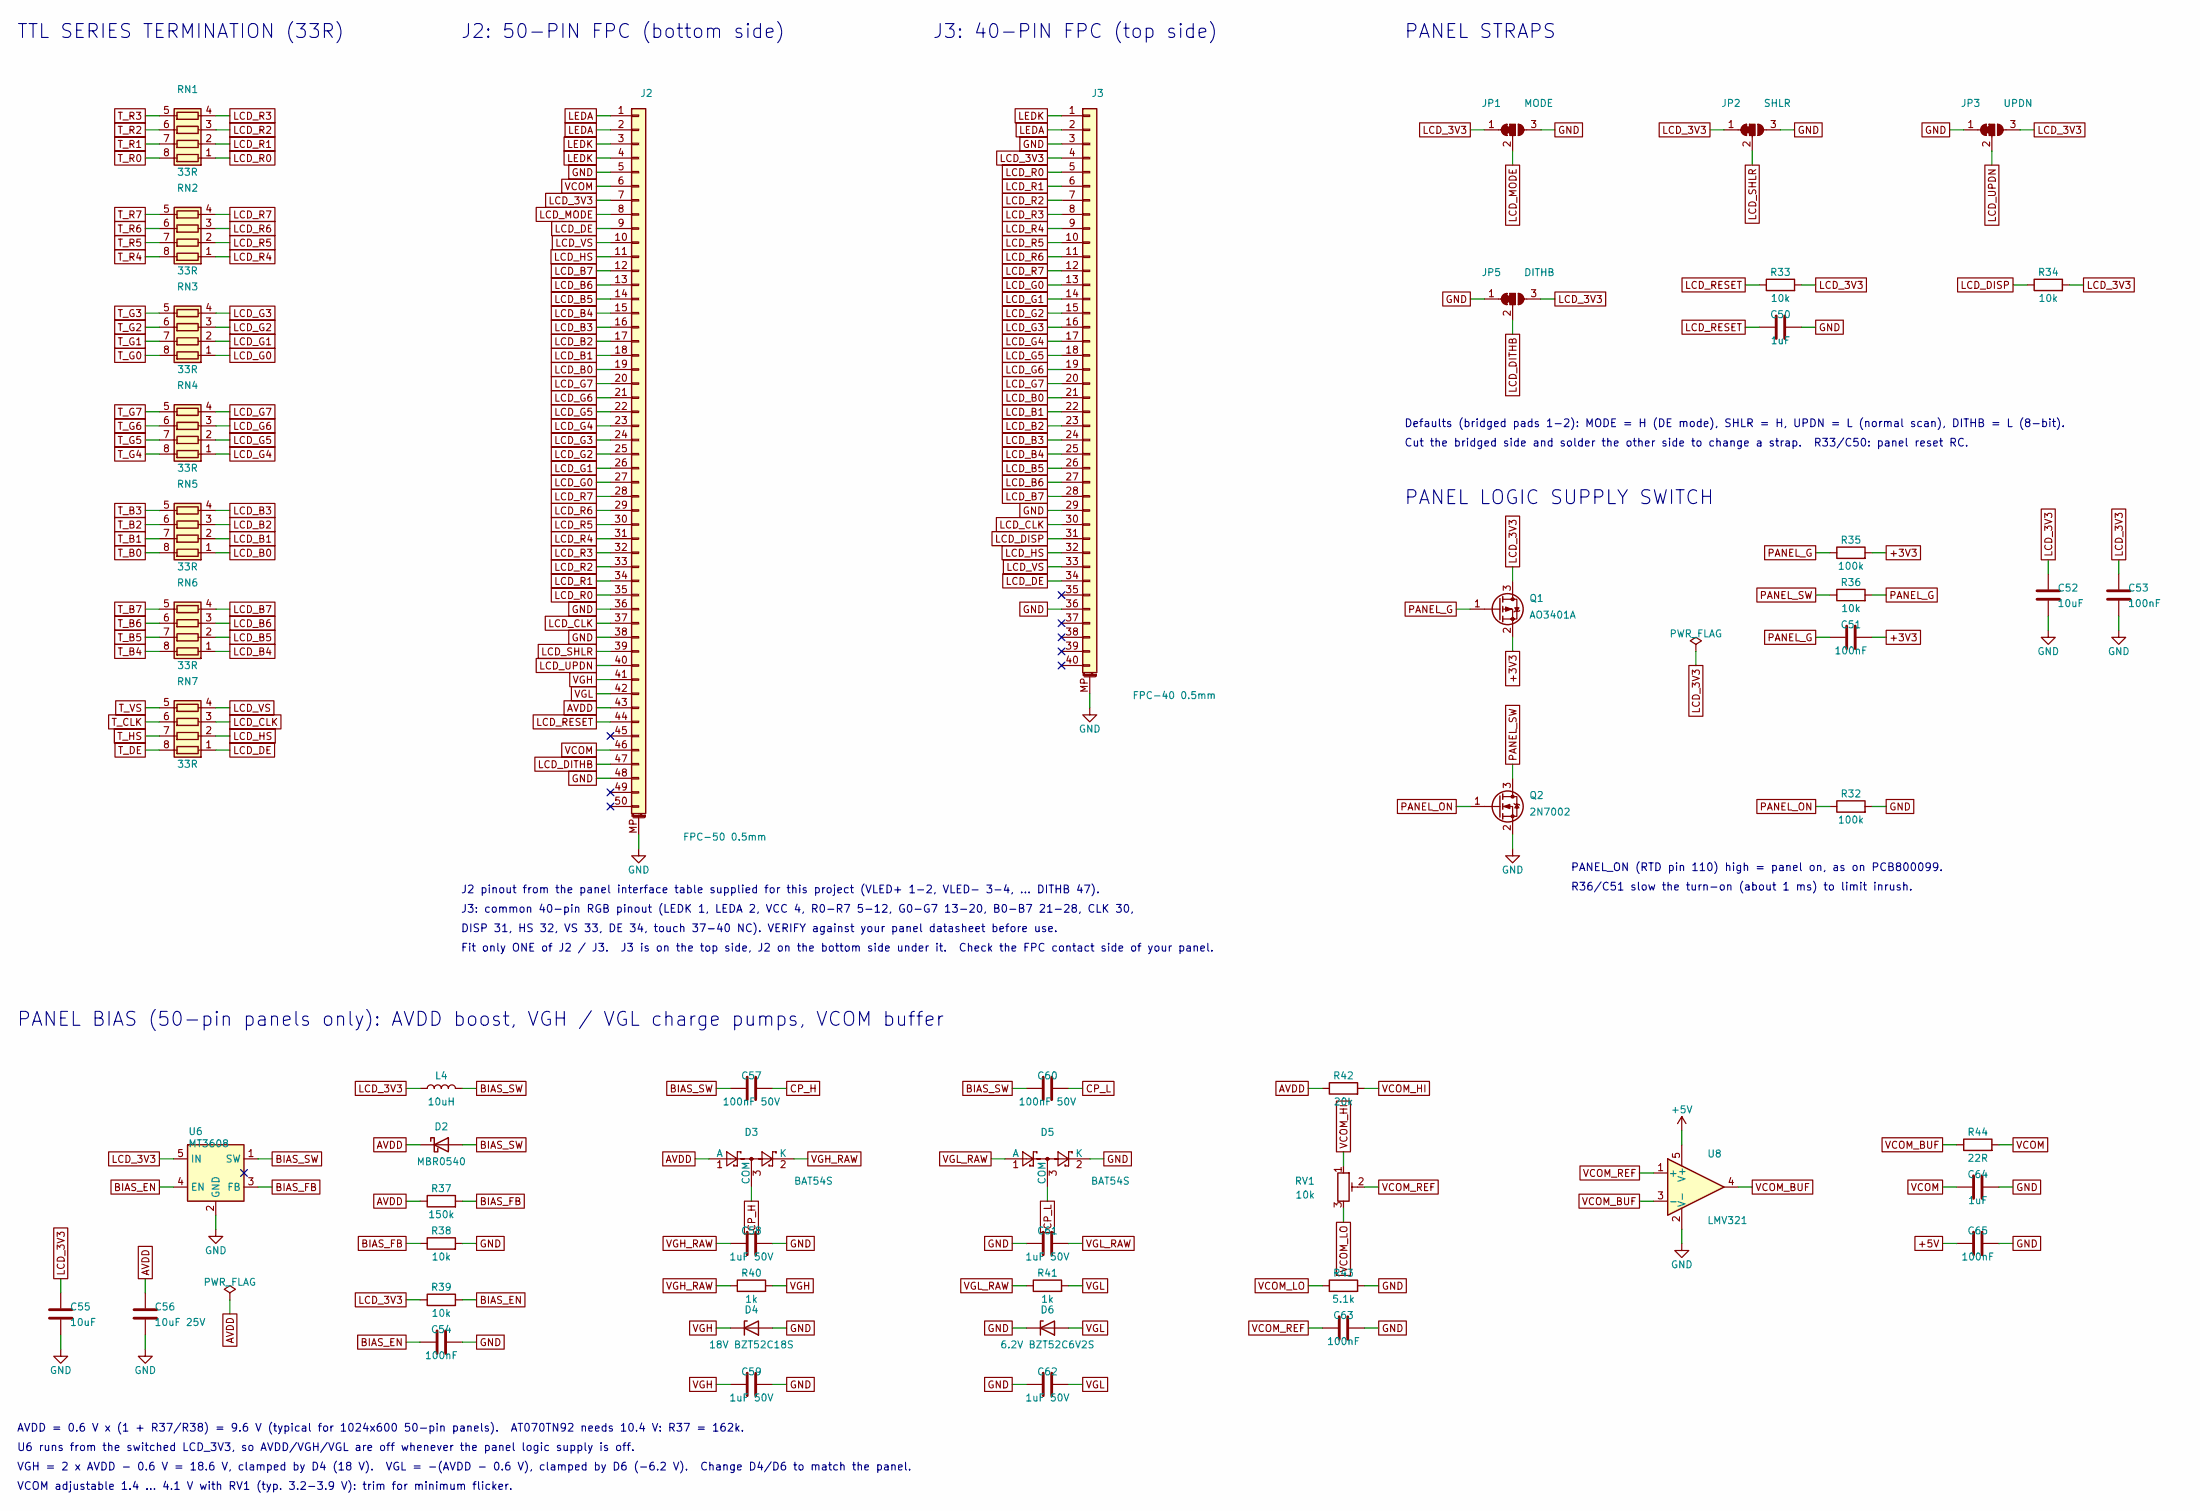
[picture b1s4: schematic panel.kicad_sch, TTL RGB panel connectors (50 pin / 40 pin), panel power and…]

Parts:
C50, C64: 1uF; C_0603_1608Metric
C51, C53, C54, C63, C65: 100nF; C_0603_1608Metric
C52, C55: 10uF; C_0805_2012Metric
C56: 10uF 25V; C_0805_2012Metric
C57, C60: 100nF 50V; C_0603_1608Metric
C58, C59, C61, C62: 1uF 50V; C_0805_2012Metric
D2: MBR0540; D_SOD-123
D3, D5: BAT54S; SOT-23
D4: 18V BZT52C18S; D_SOD-323
D6: 6.2V BZT52C6V2S; D_SOD-323
J2: FPC-50 0.5mm; Hirose_FH12-50S-0.5SH_1x50-1MP_P0.50mm_Horizontal
J3: FPC-40 0.5mm; Hirose_FH12-40S-0.5SH_1x40-1MP_P0.50mm_Horizontal
JP1: MODE; SolderJumper-3_P1.3mm_Bridged12_RoundedPad1.0x1.5mm
JP2: SHLR; SolderJumper-3_P1.3mm_Bridged12_RoundedPad1.0x1.5mm
JP3: UPDN; SolderJumper-3_P1.3mm_Bridged12_RoundedPad1.0x1.5mm
JP5: DITHB; SolderJumper-3_P1.3mm_Bridged12_RoundedPad1.0x1.5mm
L4: 10uH; L_Taiyo-Yuden_NR-40xx
Q1: AO3401A; SOT-23
Q2: 2N7002; SOT-23
R32, R35: 100k; R_0603_1608Metric
R33, R34, R36, R38, R39: 10k; R_0603_1608Metric
R37: 150k; R_0603_1608Metric
R40, R41: 1k; R_0603_1608Metric
R42: 20k; R_0603_1608Metric
R43: 5.1k; R_0603_1608Metric
R44: 22R; R_0603_1608Metric
RN1, RN2, RN3, RN4, RN5, RN6, RN7: 33R; R_Array_Convex_4x0603
RV1: 10k; Potentiometer_Bourns_TC33X_Vertical
U6: MT3608; SOT-23-6
U8: LMV321; SOT-23-5

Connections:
+3V3: C51.2, Q1.2 (S), R35.2; also elsewhere on the board
+5V: C65.1, U8.5 (V+); also elsewhere on the board
AVDD: C56.1, D2.1 (K), D3.1 (A), J2.43, R37.1, R42.1
BIAS_EN: C54.1, R39.2, U6.4 (EN)
BIAS_FB: R37.2, R38.1, U6.3 (FB)
BIAS_SW: C57.1, C60.1, D2.2 (A), L4.2, U6.1 (SW)
CP_H: C57.2, D3.3 (COM)
CP_L: C60.2, D5.3 (COM)
GND: C50.2, C52.2, C53.2, C54.2, C55.2, C56.2, C58.2, C59.2, C61.1, C62.1, C63.2, C64.2, C65.2, D4.2 (A), D5.2 (K), D6.1 (K), J2.5, J2.36, J2.38, J2.48, J2.MP (MountPin), J3.3, J3.29, J3.36, J3.MP (MountPin), JP1.3 (B), JP2.3 (B), JP3.1 (A), JP5.1 (A), Q2.2 (S), R32.2, R38.2, R43.2, U6.2 (GND), U8.2 (V-); also elsewhere on the board
LCD_3V3: C52.1, C53.1, C55.1, J2.7, J3.4, JP1.1 (A), JP2.1 (A), JP3.3 (B), JP5.3 (B), L4.1, Q1.3 (D), R33.2, R34.2, R39.1, U6.5 (IN)
LCD_B0: J2.19, J3.21, RN5.1 (R1.1)
LCD_B1: J2.18, J3.22, RN5.2 (R2.1)
LCD_B2: J2.17, J3.23, RN5.3 (R3.1)
LCD_B3: J2.16, J3.24, RN5.4 (R4.1)
LCD_B4: J2.15, J3.25, RN6.1 (R1.1)
LCD_B5: J2.14, J3.26, RN6.2 (R2.1)
LCD_B6: J2.13, J3.27, RN6.3 (R3.1)
LCD_B7: J2.12, J3.28, RN6.4 (R4.1)
LCD_CLK: J2.37, J3.30, RN7.3 (R3.1)
LCD_DE: J2.9, J3.34, RN7.1 (R1.1)
LCD_DISP: J3.31, R34.1
LCD_DITHB: J2.47, JP5.2 (C)
LCD_G0: J2.27, J3.13, RN3.1 (R1.1)
LCD_G1: J2.26, J3.14, RN3.2 (R2.1)
LCD_G2: J2.25, J3.15, RN3.3 (R3.1)
LCD_G3: J2.24, J3.16, RN3.4 (R4.1)
LCD_G4: J2.23, J3.17, RN4.1 (R1.1)
LCD_G5: J2.22, J3.18, RN4.2 (R2.1)
LCD_G6: J2.21, J3.19, RN4.3 (R3.1)
LCD_G7: J2.20, J3.20, RN4.4 (R4.1)
LCD_HS: J2.11, J3.32, RN7.2 (R2.1)
LCD_MODE: J2.8, JP1.2 (C)
LCD_R0: J2.35, J3.5, RN1.1 (R1.1)
LCD_R1: J2.34, J3.6, RN1.2 (R2.1)
LCD_R2: J2.33, J3.7, RN1.3 (R3.1)
LCD_R3: J2.32, J3.8, RN1.4 (R4.1)
LCD_R4: J2.31, J3.9, RN2.1 (R1.1)
LCD_R5: J2.30, J3.10, RN2.2 (R2.1)
LCD_R6: J2.29, J3.11, RN2.3 (R3.1)
LCD_R7: J2.28, J3.12, RN2.4 (R4.1)
LCD_RESET: C50.1, J2.44, R33.1
LCD_SHLR: J2.39, JP2.2 (C)
LCD_UPDN: J2.40, JP3.2 (C)
LCD_VS: J2.10, J3.33, RN7.4 (R4.1)
LEDA: J2.1, J2.2, J3.2; also elsewhere on the board
LEDK: J2.3, J2.4, J3.1; also elsewhere on the board
PANEL_G: C51.1, Q1.1 (G), R35.1, R36.2
PANEL_ON: Q2.1 (G), R32.1; also elsewhere on the board
PANEL_SW: Q2.3 (D), R36.1
T_B0: RN5.8 (R1.2); also elsewhere on the board
T_B1: RN5.7 (R2.2); also elsewhere on the board
T_B2: RN5.6 (R3.2); also elsewhere on the board
T_B3: RN5.5 (R4.2); also elsewhere on the board
T_B4: RN6.8 (R1.2); also elsewhere on the board
T_B5: RN6.7 (R2.2); also elsewhere on the board
T_B6: RN6.6 (R3.2); also elsewhere on the board
T_B7: RN6.5 (R4.2); also elsewhere on the board
T_CLK: RN7.6 (R3.2); also elsewhere on the board
T_DE: RN7.8 (R1.2); also elsewhere on the board
T_G0: RN3.8 (R1.2); also elsewhere on the board
T_G1: RN3.7 (R2.2); also elsewhere on the board
T_G2: RN3.6 (R3.2); also elsewhere on the board
T_G3: RN3.5 (R4.2); also elsewhere on the board
T_G4: RN4.8 (R1.2); also elsewhere on the board
T_G5: RN4.7 (R2.2); also elsewhere on the board
T_G6: RN4.6 (R3.2); also elsewhere on the board
T_G7: RN4.5 (R4.2); also elsewhere on the board
T_HS: RN7.7 (R2.2); also elsewhere on the board
T_R0: RN1.8 (R1.2); also elsewhere on the board
T_R1: RN1.7 (R2.2); also elsewhere on the board
T_R2: RN1.6 (R3.2); also elsewhere on the board
T_R3: RN1.5 (R4.2); also elsewhere on the board
T_R4: RN2.8 (R1.2); also elsewhere on the board
T_R5: RN2.7 (R2.2); also elsewhere on the board
T_R6: RN2.6 (R3.2); also elsewhere on the board
T_R7: RN2.5 (R4.2); also elsewhere on the board
T_VS: RN7.5 (R4.2); also elsewhere on the board
VCOM: C64.1, J2.6, J2.46, R44.2
VCOM_BUF: R44.1, U8.3 (-), U8.4
VCOM_HI: R42.2, RV1.1
VCOM_LO: R43.1, RV1.3
VCOM_REF: C63.1, RV1.2, U8.1 (+)
VGH: C59.1, D4.1 (K), J2.41, R40.2
VGH_RAW: C58.1, D3.2 (K), R40.1
VGL: C62.2, D6.2 (A), J2.42, R41.2
VGL_RAW: C61.2, D5.1 (A), R41.1

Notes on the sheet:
TTL SERIES TERMINATION (33R)
J2: 50-PIN FPC (bottom side)
J3: 40-PIN FPC (top side)
J2 pinout from the panel interface table supplied for this project (VLED+ 1-2, VLED- 3-4, ... DITHB 47).
J3: common 40-pin RGB pinout (LEDK 1, LEDA 2, VCC 4, R0-R7 5-12, G0-G7 13-20, B0-B7 21-28, CLK 30,
DISP 31, HS 32, VS 33, DE 34, touch 37-40 NC). VERIFY against your panel datasheet before use.
Fit only ONE of J2 / J3. J3 is on the top side, J2 on the bottom side under it. Check the FPC contact side of your panel.
PANEL STRAPS
Defaults (bridged pads 1-2): MODE = H (DE mode), SHLR = H, UPDN = L (normal scan), DITHB = L (8-bit).
Cut the bridged side and solder the other side to change a strap. R33/C50: panel reset RC.
PANEL LOGIC SUPPLY SWITCH
PANEL_ON (RTD pin 110) high = panel on, as on PCB800099.
R36/C51 slow the turn-on (about 1 ms) to limit inrush.
PANEL BIAS (50-pin panels only): AVDD boost, VGH / VGL charge pumps, VCOM buffer
AVDD = 0.6 V x (1 + R37/R38) = 9.6 V (typical for 1024x600 50-pin panels). AT070TN92 needs 10.4 V: R37 = 162k.
U6 runs from the switched LCD_3V3, so AVDD/VGH/VGL are off whenever the panel logic supply is off.
VGH = 2 x AVDD - 0.6 V = 18.6 V, clamped by D4 (18 V). VGL = -(AVDD - 0.6 V), clamped by D6 (-6.2 V). Change D4/D6 to match the panel.
VCOM adjustable 1.4 ... 4.1 V with RV1 (typ. 3.2-3.9 V): trim for minimum flicker.

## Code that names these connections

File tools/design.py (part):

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R('R47', '100k', 'BL_DIM', 'BL_FB', S1, 378.46, 106.68)
note(S1, 202, 126, 'I_LED(max) = 0.214 V / Rset.  R7 only: 42 mA (JP4 open, default).  JP4 closed (R7 || R8 = 1.63R): 131 mA.')
note(S1, 202, 130, 'Typical 7" 1024x600 50-pin panels: 9.6 V, 120-140 mA (3 LEDs in series x 6-7 strings). Check your panel, then close JP4.')
note(S1, 202, 134, 'BL_EN_N (RTD pin 111) low = on: Q3 releases CTRL.  R9 keeps the backlight off while the RTD2660 is in reset.')
note(S1, 202, 138, 'Dimming: PWM0 (RTD pin 102) is filtered by R46/C14 and summed into FB by R47: higher duty = dimmer, 100 % = off.')
note(S1, 202, 142, 'For direct PWM on CTRL (5-100 kHz) remove R10 and R47 and fit R11.  Open-LED clamp is 38 V: C11, D1 rated >= 40 V.')
for i in range(4):
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d.add('J4', 'Connector_Generic:Conn_01x07', 'FLASH PROG', 'Connector_PinHeader_1.27mm:PinHeader_1x07_P1.27mm_Vertical',
      {1: '+3V3', 2: 'FLASH_CS', 3: 'FLASH_DO', 4: 'FLASH_DI', 5: 'FLASH_CLK', 6: 'GND', 7: 'RESETB'}, S2, (391.16, 45.72),
      ref_at=(391.16, 37.5, 0, None), val_at=(393.5, 58.5, 0, None))
note(S2, 290, 72, 'J4: in-circuit programming of U4 (hold RESETB, pin 7, low while programming).')

title(S2, 290, 84, 'SETTINGS EEPROM (optional, 0xA0)')
ex, ey = 335.28, 104.14
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note(S2, 290, 208, 'J7: 1 +3V3  2 GND  3 POWER  4 MENU  5 UP  6 DOWN  7 SOURCE  8 LED1  9 LED2  10 IR')
note(S2, 290, 211.5, 'Keys are plain switches to GND: the PCB800099 ADC ladder (0R / 1k / 2k / 3.9k / 10k')
note(S2, 290, 215, 'against the 4.7k pull-up R29) is on this board, read by RTD pin 53 (A-ADC3).')
note(S2, 290, 218.5, 'LED1 = RTD pin 52, LED2 = pin 65: pin high = LED on (LED from header pin to GND).')
note(S2, 290, 222, 'IR receiver output to pin 10 (RTD pin 64).')

# =====================================================================
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      'Connector_FFC-FPC:Hirose_FH12-40S-0.5SH_1x40-1MP_P0.50mm_Horizontal', j3, S3, (213.36, 83.82),
      ref_at=(214.8, 31.5, 0, None), val_at=(221, 140, 0, 'left'))
note(S3, 100, 176, 'J2 pinout from the panel interface table supplied for this project (VLED+ 1-2, VLED- 3-4, ... DITHB 47).')
note(S3, 100, 179.5, 'J3: common 40-pin RGB pinout (LEDK 1, LEDA 2, VCC 4, R0-R7 5-12, G0-G7 13-20, B0-B7 21-28, CLK 30,')
note(S3, 100, 183, 'DISP 31, HS 32, VS 33, DE 34, touch 37-40 NC). VERIFY against your panel datasheet before use.')
note(S3, 100, 186.5, 'Fit only ONE of J2 / J3.  J3 is on the top side, J2 on the bottom side under it.  Check the FPC contact side of your panel.')

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CV('C52', '10uF', 'LCD_3V3', 'GND', S3, 386.08, 121.92, fp=FP_C6)
CV('C53', '100nF', 'LCD_3V3', 'GND', S3, 398.78, 121.92)
d.flags += [(S3, 322.58, 132.08, 'LCD_3V3')]
note(S3, 300, 172, 'PANEL_ON (RTD pin 110) high = panel on, as on PCB800099.')
note(S3, 300, 175.5, 'R36/C51 slow the turn-on (about 1 ms) to limit inrush.')

title(S3, 20, 200, 'PANEL BIAS (50-pin panels only): AVDD boost, VGH / VGL charge pumps, VCOM buffer')
ux, uy = 55.88, 226.06
d.add('U6', 'Regulator_Switching:MT3608', 'MT3608', FP_SOT236,
      {1: 'BIAS_SW', 2: 'GND', 3: 'BIAS_FB', 4: 'BIAS_EN', 5: 'LCD_3V3', 6: NC}, S3, (ux, uy),
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CV('C55', '10uF', 'LCD_3V3', 'GND', S3, 27.94, 251.46, fp=FP_C6)
CV('C56', '10uF 25V', 'AVDD', 'GND', S3, 43.18, 251.46, fp=FP_C8)
d.flags += [(S3, 58.42, 248.92, 'AVDD')]
note(S3, 20, 273, 'AVDD = 0.6 V x (1 + R37/R38) = 9.6 V (typical for 1024x600 50-pin panels).  AT070TN92 needs 10.4 V: R37 = 162k.')
note(S3, 20, 276.5, 'U6 runs from the switched LCD_3V3, so AVDD/VGH/VGL are off whenever the panel logic supply is off.')

C('C57', '100nF 50V', 'BIAS_SW', 'CP_H', S3, 152.4, 210.82)
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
